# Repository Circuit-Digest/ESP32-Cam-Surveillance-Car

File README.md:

# [ESP32 Cam Surveillance Car](https://circuitdigest.com/microcontroller-projects/)

<br>

<br>

<be>

[ESP32 Cam Surveillance Car](https://circuitdigest.com/microcontroller-projects/esp32-cam-surveillance-car)

[Watch full video on ESP32 surveillance car](https://youtu.be/W6qm61QcYmw)

[<h1>Click here](https://circuitdigest.com/tags/ESP32) For other ESP32 tutorials.</h1>

<br>
<br>
<br>
<br>
In this project, we are going to build an ESP32 Cam Surveillance Car—a practical and accessible starting point to start learning about remote-controlled and ESP32 projects. This project leverages the versatility of the ESP32 camera module, offering a budget-friendly, energy-efficient and easy-to-make solution. Designed with simplicity and functionality in mind, it's an ideal starting point for newcomers to start learning web controls and the WiFi functionality of ESP32.
<br>
[Note: As this projects are very simple we are only providing the code, schemaitic, and a few essential images if you want to get the images or code explanations do check out the Circuit Digest website.
<br>
<br>

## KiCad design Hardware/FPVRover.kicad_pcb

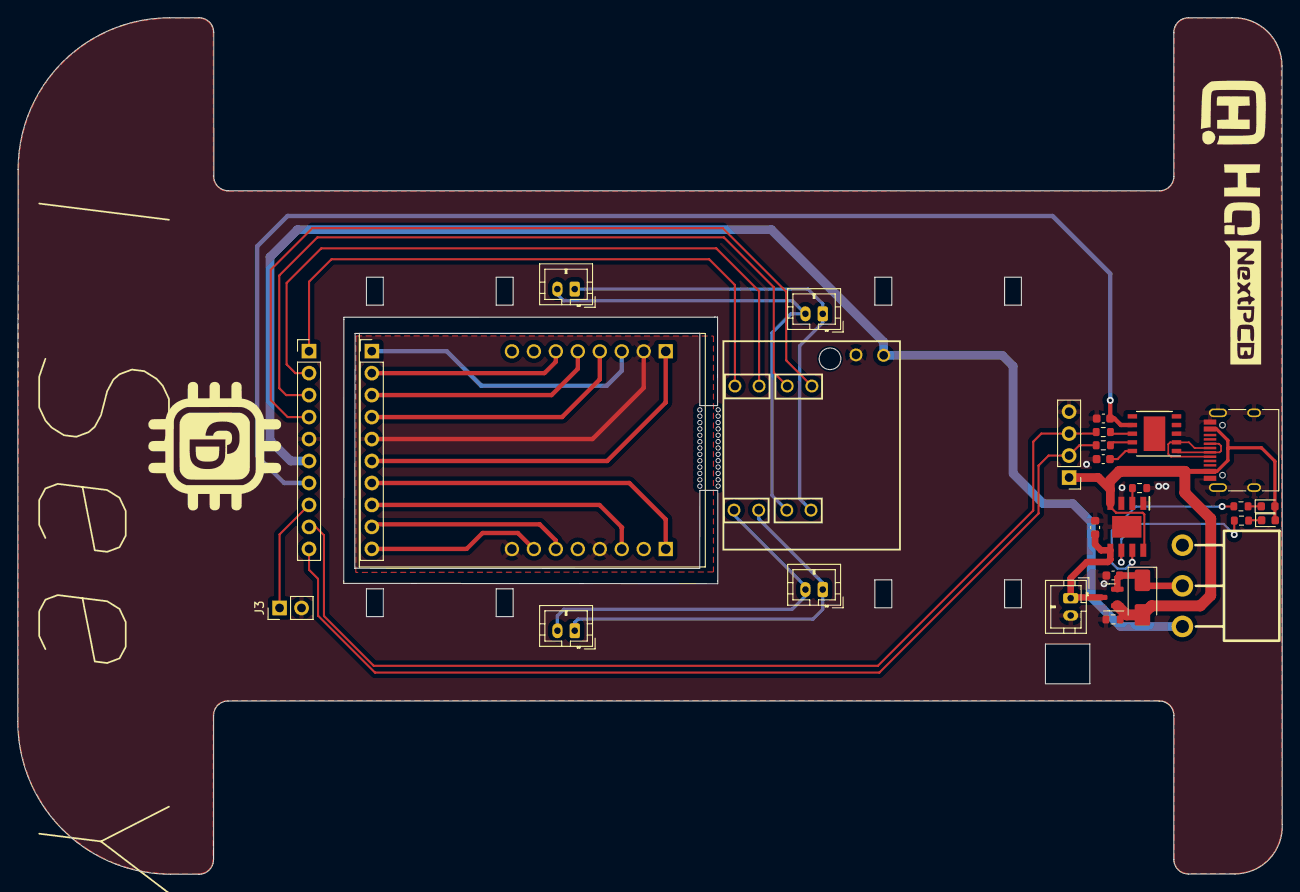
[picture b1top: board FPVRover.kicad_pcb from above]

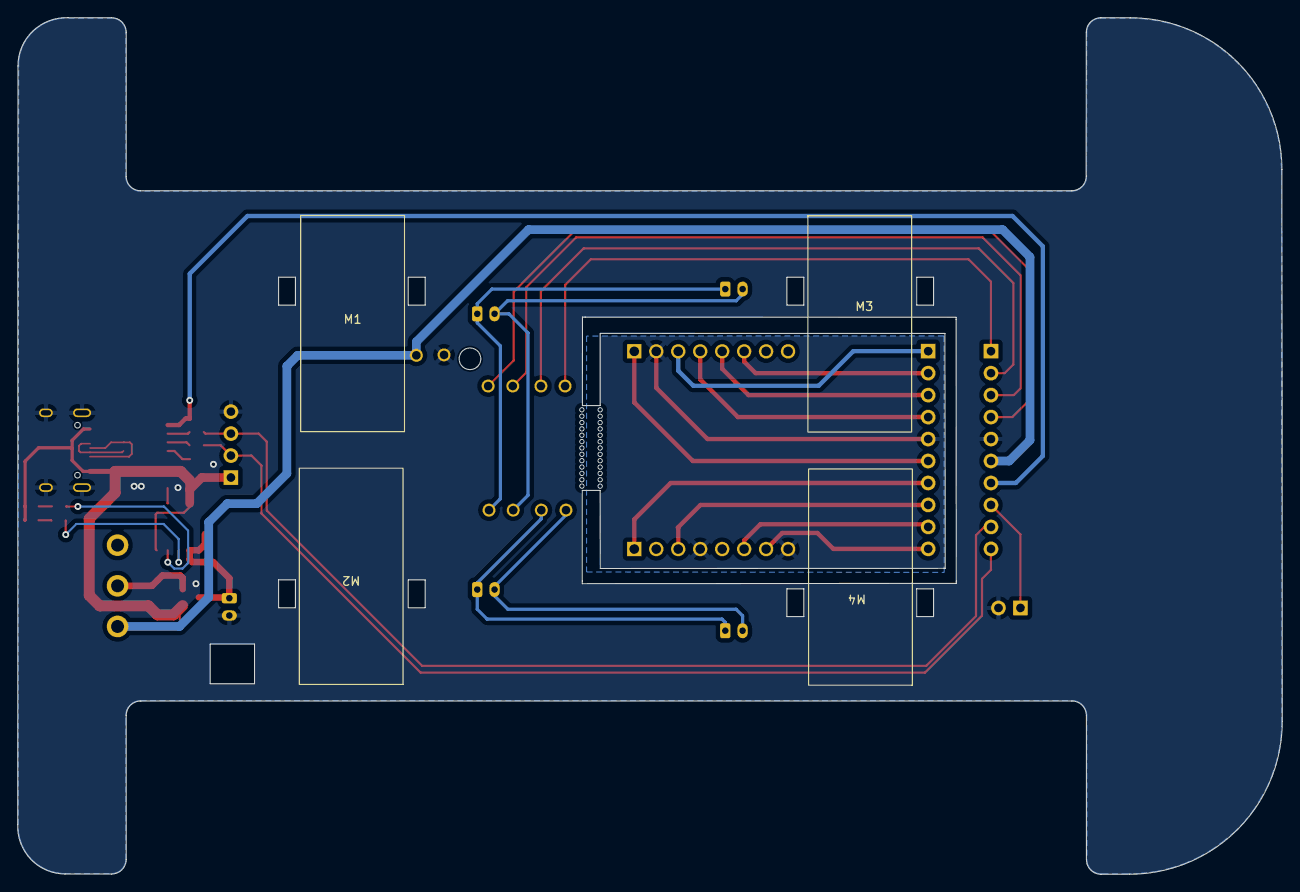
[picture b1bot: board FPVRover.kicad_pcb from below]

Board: 2 copper layers, 146.2 x 99.0 mm, 33 parts (4 on the bottom side), 37 nets.

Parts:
C1: 10u; C_0603_1608Metric
C2: 10uF; C_0603_1608Metric
C3: 0.1uf; C_0603_1608Metric
C4: 0.1UF; C_0603_1608Metric
D1: SS34; D_SMA
IC1: ESP32-CAM; ESP32CAM
IC2: TP4056; SOIC127P600X175-9N
J1: USB_C_Receptacle_USB2.0; USB_C_Receptacle_HRO_TYPE-C-31-M-12
J2: B2B-PH-SM4-TB(LF)(SN); JST_PH_B2B-PH-K_1x02_P2.00mm_Vertical
J3: Conn_01x02; PinHeader_1x02_P2.54mm_Vertical
J4, J5, J6, J7: Conn_01x02; JST_PH_B2B-PH-K_1x02_P2.00mm_Vertical
J8: UART; PinHeader_1x04_P2.54mm_Vertical
J9, J10: Conn_01x10; PinHeader_1x10_P2.54mm_Vertical
LED1, LED2: CHG; LED_0603_1608Metric
M1, M2, M3, M4: N20
R1, R2: 1.3K; R_0603_1608Metric
R3, R4: 1K; R_0603_1608Metric
Rprog1: 1.2K; R_0603_1608Metric
SW1: SW_SPDT; SlideSwitch12mm3A
U1: MX1508; MX1508 Module
U2: 100K; R_0603_1608Metric
U3: AO3041; SOT-23
U4: ch340k; ESSOP-10_3.9x4.9mm_P1.00mm

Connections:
+3.3V: C4.2, J9.7, U4.7 (VCC)
+3V3: IC1.9 (3V3), J10.7
+5V: D1.2 (A), IC2.4 (VCC), IC2.8 (CE), J1.A4 (VBUS), J1.A9 (VBUS), J1.B4 (VBUS), J1.B9 (VBUS), J8.1, LED1.2 (A), LED2.2 (A), U2.1, U3.1 (G)
+BATT: C2.1, IC2.5 (BAT), J2.1, U3.3 (D)
/D+: J1.A6 (D+), J1.B6 (D+), U4.1 (D+)
/D-: J1.A7 (D-), J1.B7 (D-), U4.2 (D-)
/IN1: J9.4, U1.3 (IN1)
/IN1a: IC1.5 (IO13), J10.4
/IN2: J9.3, U1.4 (IN2)
/IN2a: IC1.4 (IO15), J10.3
/IN3: J9.2, U1.5 (IN3)
/IN3a: IC1.3 (IO14), J10.2
/IN4: J9.1, U1.6 (IN4)
/IN4a: IC1.6 (IO12), J10.1
/IO0: IC1.11 (IO0), J10.8
/RX: J8.3, J9.9, R4.1
/RX1: IC1.14 (U0R), J10.9
/TX: J8.2, J9.10, R3.1
/TX1: IC1.15 (U0T), J10.10
GND: C1.2, C2.2, C3.1, C4.1, IC2.1 (TEMP), IC2.3 (GND), IC2.9 (EP), J1.A1 (GND), J1.A12 (GND), J1.B1 (GND), J1.B12 (GND), J1.S1 (SHIELD), J2.2, J3.2, J8.4, J9.5, Rprog1.2, U1.2 (GND), U2.2, U4.3 (GND)
GND1: IC1.7 (GND_1), IC1.12 (GND_2), IC1.16 (GND_3), J10.5
unnamed: C1.1, D1.1 (K), SW1.2 (B), U3.2 (S)
unnamed: IC2.2 (PROG), Rprog1.1
unnamed: IC2.7 (~CHRG), R1.2
unnamed: IC2.6 (~STDBY), R2.2
unnamed: J3.1, J9.8
unnamed: J4.1, J6.1, U1.7 (M1A)
unnamed: J4.2, J6.2, U1.8 (M1B)
unnamed: J5.1, J7.1, U1.9 (M2A)
unnamed: J5.2, J7.2, U1.10 (M2B)
unnamed: LED1.1 (K), R1.1
unnamed: LED2.1 (K), R2.1
unnamed: R3.2, U4.9 (RXD)
unnamed: R4.2, U4.8 (TXD)
unnamed: C3.2, U4.10 (V3)
VBUS: J9.6, SW1.3 (C), U1.1 (VCC)
VDD: IC1.8 (5V), J10.6

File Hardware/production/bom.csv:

Designator,Footprint,Quantity,Value,LCSC Part #
C1,0603,1,10u,
C2,0603,1,10uF,
"C3, C4",0603,2,0.1uf,
D1,D_SMA,1,SS34,
IC1,ESP32CAM,1,ESP32-CAM,
IC2,SOIC127P600X175-9N,1,TP4056,
J1,USB_C_Receptacle_HRO_TYPE-C-31-M-12,1,USB_C_Receptacle_USB2.0,
"J10, J9",PinHeader_1x10_P2.54mm_Vertical,2,Conn_01x10,
J2,JST_PH_B2B-PH-K_1x02_P2.00mm_Vertical,1, B2B-PH-SM4-TB(LF)(SN) ,
J3,PinHeader_1x02_P2.54mm_Vertical,1,Conn_01x02,
"J4, J5, J6, J7",JST_PH_B2B-PH-K_1x02_P2.00mm_Vertical,4,Conn_01x02,
J8,PinHeader_1x04_P2.54mm_Vertical,1,UART,
"LED1, LED2",0603,2,CHG,
"M1, M2, M3, M4",N20,4,~,
"R1, R2",0603,2,1.3K,
"R3, R4",0603,2,1K,
Rprog1,0603,1,1.2K,
SW1,SlideSwitch12mm3A,1,SW_SPDT,
U1,MX1508 Module,1,MX1508,
U2,0603,1,100K,
U3,SOT-23,1,AO3041,
U4,ESSOP-10_3.9x4.9mm_P1.00mm,1,ch340k,

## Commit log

2024-03-27 Create j
